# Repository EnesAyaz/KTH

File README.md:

# KTH
This repository is opened to be archival information for my coming Ph.D studies at KTH.

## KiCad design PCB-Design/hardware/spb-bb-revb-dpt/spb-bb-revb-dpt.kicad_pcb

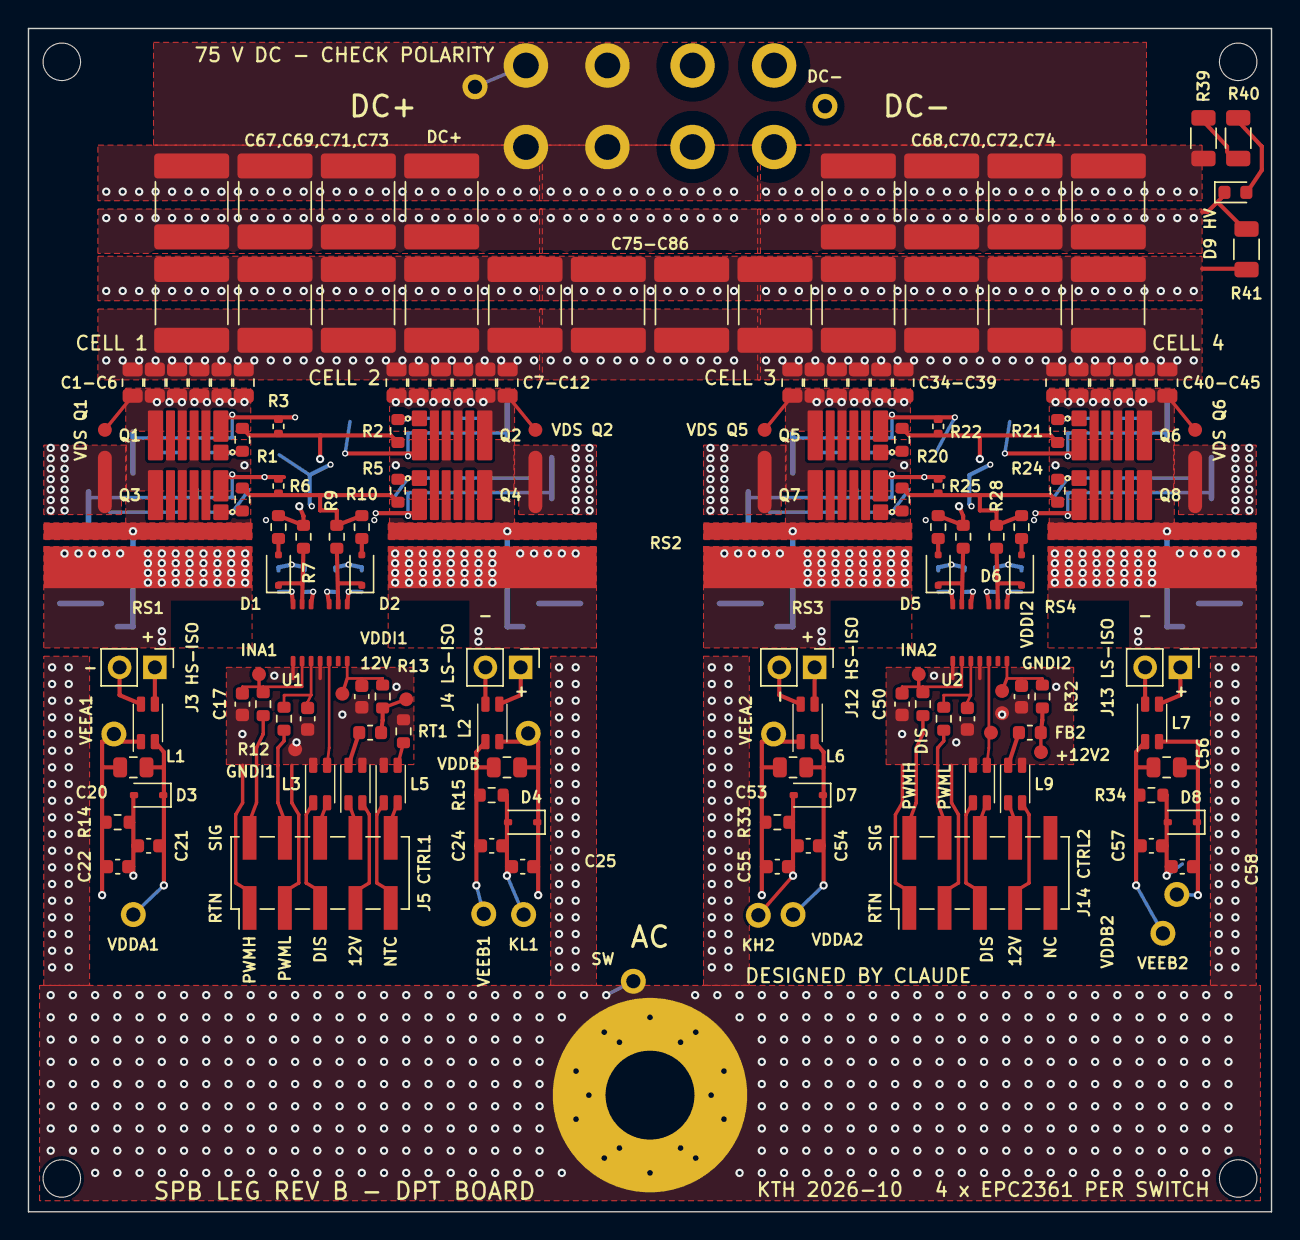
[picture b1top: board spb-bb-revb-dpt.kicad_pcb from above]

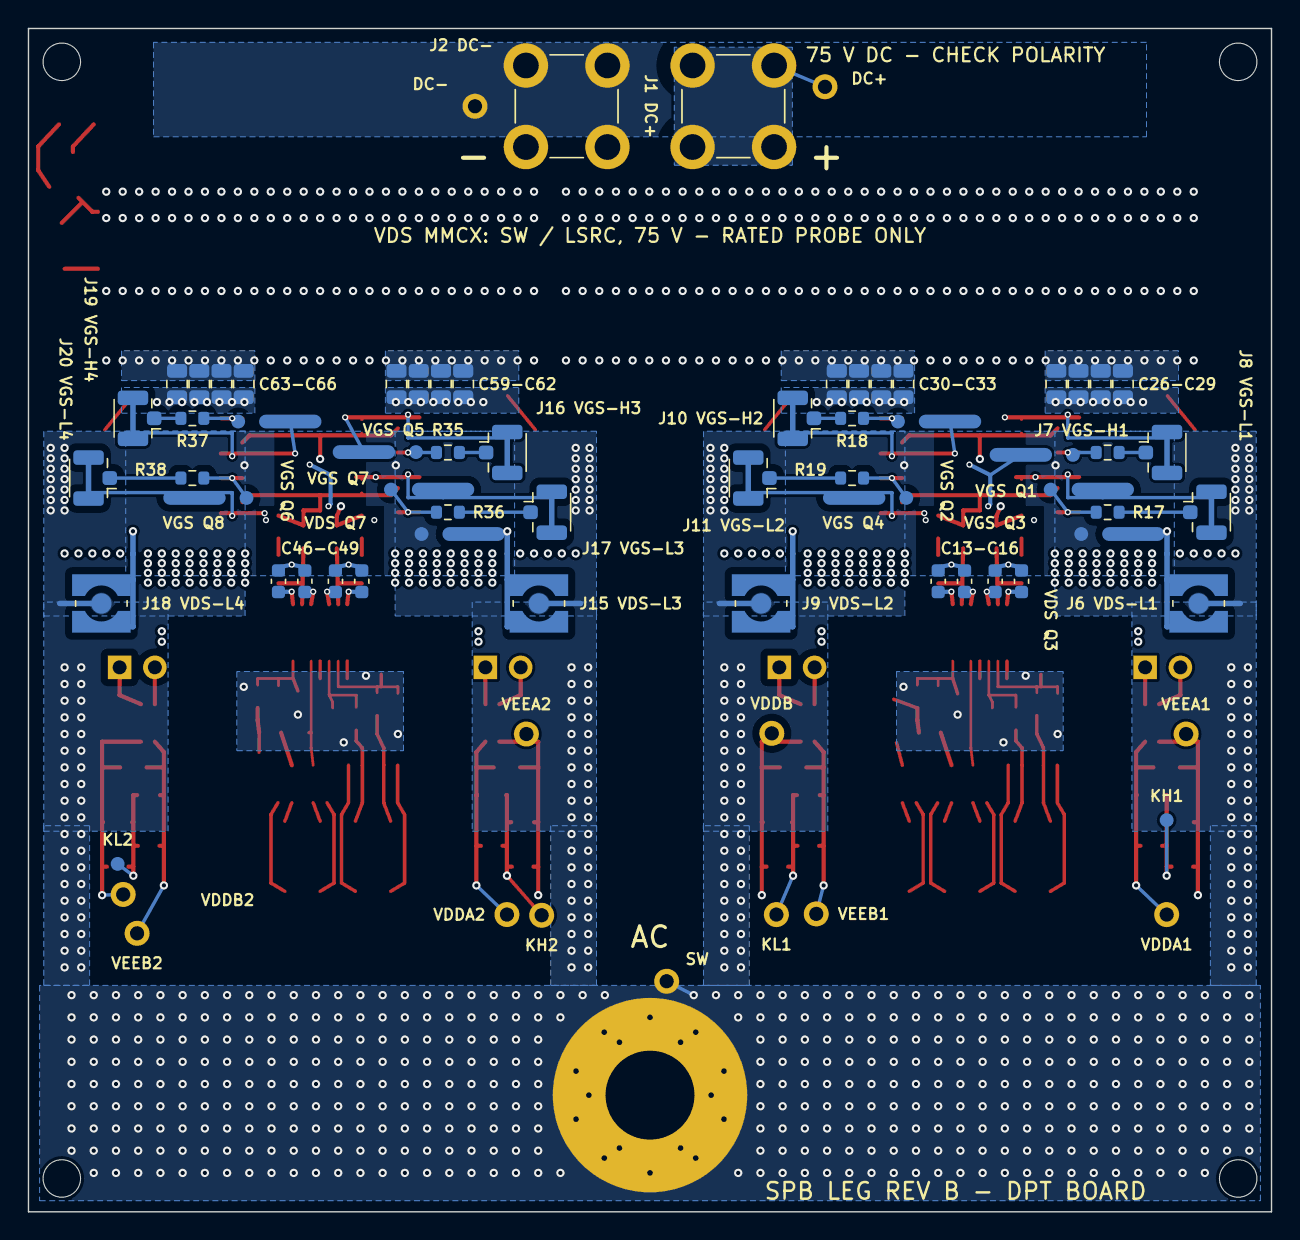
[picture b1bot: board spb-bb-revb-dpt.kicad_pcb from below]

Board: 4 copper layers, 89.5 x 85.2 mm, 225 parts (67 on the bottom side), 86 nets.

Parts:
C1, C2, C3, C4, C5, C6, C7, C8, C9, C10, C11, C12, C26, C27, C28, C29, C30, C31, C32, C33, C34, C35, C36, C37, C38, C39, C40, C41, C42, C43, C44, C45, C59, C60, C61, C62, C63, C64, C65, C66: 1uF 100V X7S; C_0805_2012Metric_TightCrtYd
C13, C14, C15, C16, C46, C47, C48, C49: 1uF 25V X7R 0603; C_0603_1608Metric
C17, C18, C50, C51: 100pF C0G 0603; C_0603_1608Metric
C19, C52: 22nF 25V X7R 0603; C_0603_1608Metric
C20, C23, C53, C56: 4.7uF 25V X7R 0805; C_0805_2012Metric
C21, C22, C24, C25, C54, C55, C57, C58: 4.7uF 16V X5R 0603; C_0603_1608Metric
C67, C68, C69, C70, C71, C72, C73, C74, C75, C76, C77, C78, C79, C80, C81, C82, C83, C84, C85, C86: 22uF 100V X7S 2220; C_2220_5750Metric_TightCrtYd
D1, D2, D5, D6: PMEG3020EJ; D_SOD-323F
D3, D4, D7, D8: BZX384-C5V1; D_SOD-323
D9: red 0603 (DC link present); LED_0603_1608Metric
FB1, FB2: BLM18PG221SN1 (220 R @ 100 MHz); L_0603_1608Metric
H1, H2, H3, H4: M2.5 insulated; MountingHole_2.7mm_M2.5
J1: DC+; Wuerth_REDCUBE-THR_WP-THRBU_74650174_THR
J2: DC-; Wuerth_REDCUBE-THR_WP-THRBU_74650174_THR
J3, J12: V_ISO,HS in: 1 +, 2 -; PinHeader_1x02_P2.54mm_Vertical
J4, J13: V_ISO,LS in: 1 +, 2 -; PinHeader_1x02_P2.54mm_Vertical
J5: CTRL1: 1 RTN 2 PWMH 3 RTN 4 PWML 5 RTN 6 DIS 7 RT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; PinHeader_2x05_P2.54mm_Vertical_SMD
J6: MMCX VDS L1; WR-MMCX_Wuerth_66012102111404_Vertical
J7: U.FL H1; U.FL_Hirose_U.FL-R-SMT-1_Vertical
J8: U.FL L1; U.FL_Hirose_U.FL-R-SMT-1_Vertical
J9: MMCX VDS L2; WR-MMCX_Wuerth_66012102111404_Vertical
J10: U.FL H2; U.FL_Hirose_U.FL-R-SMT-1_Vertical
J11: U.FL L2; U.FL_Hirose_U.FL-R-SMT-1_Vertical
J14: CTRL2: 1 RTN 2 PWMH 3 RTN 4 PWML 5 RTN 6 DIS 7 RT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; PinHeader_2x05_P2.54mm_Vertical_SMD
J15: MMCX VDS L3; WR-MMCX_Wuerth_66012102111404_Vertical
J16: U.FL H3; U.FL_Hirose_U.FL-R-SMT-1_Vertical
J17: U.FL L3; U.FL_Hirose_U.FL-R-SMT-1_Vertical
J18: MMCX VDS L4; WR-MMCX_Wuerth_66012102111404_Vertical
J19: U.FL H4; U.FL_Hirose_U.FL-R-SMT-1_Vertical
J20: U.FL L4; U.FL_Hirose_U.FL-R-SMT-1_Vertical
J21: AC; AC_BOLT_M6
L1, L2, L3, L4, L5, L6, L7, L8, L9: WE-CNSW 744232601; L_CommonMode_Wurth_WE-CNSW-1206
Q1, Q2, Q3, Q4, Q5, Q6, Q7, Q8: EPC2361
R1, R20: 0R5 1% (R_G HL); R_0603_1608Metric
R2, R21: 0R5 1% (R_G HR); R_0603_1608Metric
R3, R22: 10k 1% (HS gate pull-down); R_0402_1005Metric
R4, R23: 0R5 1% (R_G LL); R_0603_1608Metric
R5, R24: 0R5 1% (R_G LR); R_0603_1608Metric
R6, R25: 10k 1% (LS gate pull-down); R_0402_1005Metric
R7, R26: 1R5 1% (R_ON,A); R_0603_1608Metric
R8, R27: 0R (R_OFF,A); R_0603_1608Metric
R9, R28: 1R5 1% (R_ON,B); R_0603_1608Metric
R10, R29: 0R (R_OFF,B); R_0603_1608Metric
R11, R30: 47R 1% (INA); R_0603_1608Metric
R12, R31: 47R 1% (INB); R_0603_1608Metric
R13, R32: 3k 1% (RVDDI); R_0603_1608Metric
R14, R15, R33, R34: 150R 1% 0603 (bias, <= 82 mW); R_0603_1608Metric
R16, R18, R35, R37: DNP 0R (V_GS HS, fit to use the U.FL); R_0603_1608Metric
R17, R19, R36, R38: DNP 0R (V_GS LS, fit to use the U.FL); R_0603_1608Metric
R39, R40: 68k 1206 (HV LED); R_1206_3216Metric
R41: 100k 1206 (bleeder); R_1206_3216Metric
RS1, RS2, RS3, RS4: UFCS-R001; PMK_UFCS_R001_short_IN
RT1: NTC 10k B3380 0603; R_0603_1608Metric
TP1: GNDI1; TestPoint_Pad_D1.0mm
TP2: +12V1; TestPoint_Pad_D1.0mm
TP3: VDDI1; TestPoint_Pad_D1.0mm
TP4: INA1; TestPoint_Pad_D1.0mm
TP7: VDDA1; TestPoint_Keystone5000_Adafruit3825
TP8: VEEA1; TestPoint_Keystone5000_Adafruit3825
TP9: KH1; TestPoint_Pad_D1.0mm
TP11: VDDB1; TestPoint_Keystone5000_Adafruit3825
TP12: VEEB1; TestPoint_Keystone5000_Adafruit3825
TP13: KL1; TestPoint_Keystone5000_Adafruit3825
TP15: VGS Q1; TestPoint_Spring_1.0_GND1.5-6.0
TP16: VGS Q2; TestPoint_Spring_1.0_GND1.5-6.0
TP17: VGS Q3; TestPoint_Spring_1.0_GND1.5-6.0
TP18: VGS Q4; TestPoint_Spring_1.0_GND1.5-6.0
TP19: GNDI2; TestPoint_Pad_D1.0mm
TP20: +12V2; TestPoint_Pad_D1.0mm
TP21: VDDI2; TestPoint_Pad_D1.0mm
TP22: INA2; TestPoint_Pad_D1.0mm
TP24: DIS2; TestPoint_Pad_D1.0mm
TP25: VDDA2; TestPoint_Keystone5000_Adafruit3825
TP26: VEEA2; TestPoint_Keystone5000_Adafruit3825
TP27: KH2; TestPoint_Keystone5000_Adafruit3825
TP29: VDDB2; TestPoint_Keystone5000_Adafruit3825
TP30: VEEB2; TestPoint_Keystone5000_Adafruit3825
TP31: KL2; TestPoint_Pad_D1.0mm
TP33: VGS Q5; TestPoint_Spring_1.0_GND1.5-6.0
TP34: VGS Q6; TestPoint_Spring_1.0_GND1.5-6.0
TP35: VGS Q7; TestPoint_Spring_1.0_GND1.5-6.0
TP36: VGS Q8; TestPoint_Spring_1.0_GND1.5-6.0
TP37: VDS Q3; TestPoint_Spring_1.0_GND1.5-6.0
TP38: VDS Q1; TestPoint_Spring_1.0_GND1.5-6.0
TP40: VDS Q2; TestPoint_Spring_1.0_GND1.5-6.0
TP41: VDS Q7; TestPoint_Spring_1.0_GND1.5-6.0
TP42: VDS Q5; TestPoint_Spring_1.0_GND1.5-6.0
TP44: VDS Q6; TestPoint_Spring_1.0_GND1.5-6.0
TP45: DC+; TestPoint_Keystone5000_Adafruit3825
TP46: DC-; TestPoint_Keystone5000_Adafruit3825
TP47: SW; TestPoint_Keystone5000_Adafruit3825
U1, U2: 2EDF7275K; 2EDF7275K_PG-TFLGA-13-4

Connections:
12V_CM1: FB1.1, L4.2
12V_CM2: FB2.1, L9.2
+12V1: FB1.2, R13.1, TP2.1
+12V2: FB2.2, R32.1, TP20.1
C_12V1: J5.8, L4.1
C_12V2: J14.8, L9.1
C_DIS1: J5.6, L3.4
C_DIS2: J14.6, L8.4
C_NTC1: J5.10, L5.4
C_RTN_12V1: J5.7, L4.4
C_RTN_12V2: J14.7, L9.4
C_RTN_DIS1: J5.5, L3.1
C_RTN_DIS2: J14.5, L8.1
C_RTN_NTC1: J5.9, L5.1
DCN: C1.2, C2.2, C3.2, C4.2, C5.2, C6.2, C7.2, C8.2, C9.2, C10.2, C11.2, C12.2, C26.1, C27.1, C28.1, C29.1, C30.1, C31.1, C32.1, C33.1, C34.2, C35.2, C36.2, C37.2, C38.2, C39.2, C40.2, C41.2, C42.2, C43.2, C44.2, C45.2, C59.1, C60.1, C61.1, C62.1, C63.1, C64.1, C65.1, C66.1, C67.1, C68.1, C69.1, C70.1, C71.1, C72.1, C73.1, C74.1, C75.1, C76.1, C77.1, C78.1, C79.1, C80.1, C81.1, C82.1, C83.1, C84.1, C85.1, C86.1, D9.1, J2.1, R41.2, RS1.2, RS2.2, RS3.2, RS4.2, TP46.1
DCP: C1.1, C2.1, C3.1, C4.1, C5.1, C6.1, C7.1, C8.1, C9.1, C10.1, C11.1, C12.1, C26.2, C27.2, C28.2, C29.2, C30.2, C31.2, C32.2, C33.2, C34.1, C35.1, C36.1, C37.1, C38.1, C39.1, C40.1, C41.1, C42.1, C43.1, C44.1, C45.1, C59.2, C60.2, C61.2, C62.2, C63.2, C64.2, C65.2, C66.2, C67.2, C68.2, C69.2, C70.2, C71.2, C72.2, C73.2, C74.2, C75.2, C76.2, C77.2, C78.2, C79.2, C80.2, C81.2, C82.2, C83.2, C84.2, C85.2, C86.2, J1.1, Q1.3, Q1.5, Q1.7, Q2.3, Q2.5, Q2.7, Q5.3, Q5.5, Q5.7, Q6.3, Q6.5, Q6.7, R39.1, R41.1, TP38.1, TP40.1, TP42.1, TP44.1, TP45.1
DIS1: L3.3, U1.5
DIS2: L8.3, TP24.1, U2.5
GH_L1: Q1.1, R1.1, R16.2, TP15.1
GH_L2: Q5.1, R20.1, R35.2, TP33.1
GH_R1: Q2.1, R2.2, R18.1, TP16.1
GH_R2: Q6.1, R21.2, R37.1, TP34.1
GH_STAR1: R1.2, R2.1, R3.1, R7.2, R8.2
GH_STAR2: R20.2, R21.1, R22.1, R26.2, R27.2
GL_L1: Q3.1, R4.1, R17.2, TP17.1
GL_L2: Q7.1, R23.1, R36.2, TP35.1
GL_R1: Q4.1, R5.2, R19.1, TP18.1
GL_R2: Q8.1, R24.2, R38.1, TP36.1
GL_STAR1: R4.2, R5.1, R6.1, R9.2, R10.2
GL_STAR2: R23.2, R24.1, R25.1, R28.2, R29.2
GNDI1: C17.1, C18.1, C19.1, J5.1, J5.3, L3.2, L4.3, L5.2, RT1.2, TP1.1, U1.1, U1.4
GNDI2: C50.1, C51.1, C52.1, J14.1, J14.3, L8.2, L9.3, TP19.1, U2.1, U2.4
HVA: R39.2, R40.1
HVB: D9.2, R40.2
INA1: C17.2, R11.2, TP4.1, U1.2
INA2: C50.2, R30.2, TP22.1, U2.2
INB1: C18.2, R12.2, U1.3
INB2: C51.2, R31.2, U2.3
KH1: C13.1, C14.1, C21.1, C22.2, D3.2, J7.2, J10.2, Q1.2, Q2.2, R3.2, R14.2, TP9.1, TP15.2, TP16.2
KH2: C46.1, C47.1, C54.1, C55.2, D7.2, J16.2, J19.2, Q5.2, Q6.2, R22.2, R33.2, TP27.1, TP33.2, TP34.2
KL1: C15.1, C16.1, C24.2, C25.1, D4.2, J8.2, J11.2, Q3.2, Q4.2, R6.2, R15.2, TP13.1, TP17.2, TP18.2
KL2: C48.1, C49.1, C57.2, C58.1, D8.2, J17.2, J20.2, Q7.2, Q8.2, R25.2, R34.2, TP31.1, TP35.2, TP36.2
LSRC1: J6.2, Q3.4, Q3.6, RS1.1, TP37.2
LSRC2: J9.2, Q4.4, Q4.6, RS2.1
LSRC3: J15.2, Q7.4, Q7.6, RS3.1, TP41.2
LSRC4: J18.2, Q8.4, Q8.6, RS4.1
NTC: L5.3, RT1.1
OFFA1: D1.2, R8.1
OFFA2: D5.2, R27.1
OFFB1: D2.2, R10.1
OFFB2: D6.2, R29.1
OUTA1: D1.1, R7.1, U1.12
OUTA2: D5.1, R26.1, U2.12
OUTB1: D2.1, R9.1, U1.9
OUTB2: D6.1, R28.1, U2.9
PWM_H1: J5.2, R11.1
PWM_H2: J14.2, R30.1
PWM_L1: J5.4, R12.1
PWM_L2: J14.4, R31.1
SW: J6.1, J9.1, J15.1, J18.1, J21.1, Q1.4, Q1.6, Q2.4, Q2.6, Q3.3, Q3.5, Q3.7, Q4.3, Q4.5, Q4.7, Q5.4, Q5.6, Q6.4, Q6.6, Q7.3, Q7.5, Q7.7, Q8.3, Q8.5, Q8.7, TP37.1, TP38.2, TP40.2, TP41.1, TP42.2, TP44.2, TP47.1
UFL_H1: J7.1, R16.1
UFL_H2: J10.1, R18.2
UFL_H3: J16.1, R35.1
UFL_H4: J19.1, R37.2
UFL_L1: J8.1, R17.1
UFL_L2: J11.1, R19.2
UFL_L3: J17.1, R36.1
UFL_L4: J20.1, R38.2
VDDA1: C13.2, C20.2, C21.2, D3.1, L1.4, TP7.1, U1.13
VDDA2: C46.2, C53.2, C54.2, D7.1, L6.4, TP25.1, U2.13
VDDB1: C16.2, C23.2, C25.2, D4.1, L2.4, TP11.1, U1.10
VDDB2: C49.2, C56.2, C58.2, D8.1, L7.4, TP29.1, U2.10
VDDI1: C19.2, R13.2, TP3.1, U1.7
VDDI2: C52.2, R32.2, TP21.1, U2.7
VEEA1: C14.2, C20.1, C22.1, L1.1, R14.1, TP8.1, U1.11
VEEA2: C47.2, C53.1, C55.1, L6.1, R33.1, TP26.1, U2.11
VEEB1: C15.2, C23.1, C24.1, L2.1, R15.1, TP12.1, U1.8
VEEB2: C48.2, C56.1, C57.1, L7.1, R34.1, TP30.1, U2.8
VINA_N1: J3.2, L1.2
VINA_N2: J12.2, L6.2
VINA_P1: J3.1, L1.3
VINA_P2: J12.1, L6.3
VINB_N1: J4.2, L2.2
VINB_N2: J13.2, L7.2
VINB_P1: J4.1, L2.3
VINB_P2: J13.1, L7.3

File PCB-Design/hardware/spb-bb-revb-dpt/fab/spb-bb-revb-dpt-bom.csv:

"# 4 layers, 1.6 mm FR4, 2 oz (70 um) on all layers, L1-L2 and L3-L4 prepreg 0.1 mm, ENIG; filled + capped via-in-pad (list in gerber/*-fab-notes.txt: shunt SHLD, bypass-capacitor and test pads); double-pulse board (UFCS shunts, no heatsink); IPC class 2; solder mask over all copper and ALL vias tented (the 1200 V control/power barrier relies on it)"
Qty,References,Value,Footprint,Manufacturer part / note,Fit
1,J1,DC+,Wuerth_REDCUBE-THR_WP-THRBU_74650174_THR,"Wuerth 74650174 (REDCUBE THR, M4)",fit
1,J2,DC-,Wuerth_REDCUBE-THR_WP-THRBU_74650174_THR,"Wuerth 74650174 (REDCUBE THR, M4)",fit
8,Q1 Q2 Q3 Q4 Q5 Q6 Q7 Q8,EPC2361,EPC2361,EPC2361,fit
40,C1 C2 C3 C4 C5 C6 C7 C8 C9 C10 C11 C12 C26 C27 C28 C29 C30 C31 C32 C33 C34 C35 C36 C37 C38 C39 C40 C41 C42 C43 C44 C45 C59 C60 C61 C62 C63 C64 C65 C66,1uF 100V X7S,C_0805_2012Metric_TightCrtYd,TDK C2012X7S2A105K125AB,fit
2,R1 R20,0R5 1% (R_G HL),R_0603_1608Metric,0.5R 0603 1% (Panasonic ERJ-3BQFR50V),fit
2,R2 R21,0R5 1% (R_G HR),R_0603_1608Metric,0.5R 0603 1% (Panasonic ERJ-3BQFR50V),fit
2,R3 R22,10k 1% (HS gate pull-down),R_0402_1005Metric,10k 0402 1%,fit
2,R4 R23,0R5 1% (R_G LL),R_0603_1608Metric,0.5R 0603 1% (Panasonic ERJ-3BQFR50V),fit
2,R5 R24,0R5 1% (R_G LR),R_0603_1608Metric,0.5R 0603 1% (Panasonic ERJ-3BQFR50V),fit
2,R6 R25,10k 1% (LS gate pull-down),R_0402_1005Metric,10k 0402 1%,fit
2,U1 U2,2EDF7275K,2EDF7275K_PG-TFLGA-13-4,Infineon 2EDF7275KXUMA1,fit
2,R7 R26,"1R5 1% (R_ON,A)",R_0603_1608Metric,1.5R 0603 1% (Yageo RC0603FR-071R5L),fit
2,R8 R27,"0R (R_OFF,A)",R_0603_1608Metric,0R 0603 jumper (set R_OFF here),fit
4,D1 D2 D5 D6,PMEG3020EJ,D_SOD-323F,"Nexperia PMEG3020EJ (30 V, 2 A, SOD323F)",fit
2,R9 R28,"1R5 1% (R_ON,B)",R_0603_1608Metric,1.5R 0603 1% (Yageo RC0603FR-071R5L),fit
2,R10 R29,"0R (R_OFF,B)",R_0603_1608Metric,0R 0603 jumper (set R_OFF here),fit
8,C13 C14 C15 C16 C46 C47 C48 C49,1uF 25V X7R 0603,C_0603_1608Metric,TDK C1608X7R1E105K080AB,fit
4,C17 C18 C50 C51,100pF C0G 0603,C_0603_1608Metric,Murata GRM1885C1H101JA01,fit
2,R11 R30,47R 1% (INA),R_0603_1608Metric,47R 0603 1%,fit
2,R12 R31,47R 1% (INB),R_0603_1608Metric,47R 0603 1%,fit
2,C19 C52,22nF 25V X7R 0603,C_0603_1608Metric,Murata GRM188R71E223KA01,fit
2,R13 R32,3k 1% (RVDDI),R_0603_1608Metric,3.0k 0603 1%,fit
4,RS1 RS2 RS3 RS4,UFCS-R001,PMK_UFCS_R001_short_IN,"PMK UFCS-R001 (1 mOhm, 50 A cont.)","NOT by the assembler: hand-soldered in the lab at the blade (short IN land), SMA cable to the scope"
2,J3 J12,"V_ISO,HS in: 1 +, 2 -",PinHeader_1x02_P2.54mm_Vertical,2.54 mm header 1x2,fit
9,L1 L2 L3 L4 L5 L6 L7 L8 L9,WE-CNSW 744232601,L_CommonMode_Wurth_WE-CNSW-1206,"Wurth 744232601 (600 Ohm @ 100 MHz, 260 mA)",fit
4,C20 C23 C53 C56,4.7uF 25V X7R 0805,C_0805_2012Metric,Murata GRM21BR71E475KA73,fit
4,D3 D4 D7 D8,BZX384-C5V1,D_SOD-323,"Nexperia BZX384-C5V1 (5.1 V, 300 mW)",fit
4,R14 R15 R33 R34,"150R 1% 0603 (bias, <= 82 mW)",R_0603_1608Metric,150R 0603 1% 0.1 W,fit
8,C21 C22 C24 C25 C54 C55 C57 C58,4.7uF 16V X5R 0603,C_0603_1608Metric,Murata GRM188R61C475KAAJ,fit
2,J4 J13,"V_ISO,LS in: 1 +, 2 -",PinHeader_1x02_P2.54mm_Vertical,2.54 mm header 1x2,fit
1,J5,CTRL1: 1 RTN 2 PWMH 3 RTN 4 PWML 5 RTN 6 DIS 7 RTN 8 12V 9 RTN 10 NTC,PinHeader_2x05_P2.54mm_Vertical_SMD,"Samtec TSM-105-01-T-DV (2 x 5, 2.54 mm, SMT)",fit
2,FB1 FB2,BLM18PG221SN1 (220 R @ 100 MHz),L_0603_1608Metric,"Murata BLM18PG221SN1D (ferrite bead, 1.4 A)",fit
1,RT1,NTC 10k B3380 0603,R_0603_1608Metric,Murata NCP18XH103F03RB,fit
1,J6,MMCX VDS L1,WR-MMCX_Wuerth_66012102111404_Vertical,"Wurth 66012102111404 (WR-MMCX PCB SMT jack, vertical, 170 V rms)",fit
1,J7,U.FL H1,U.FL_Hirose_U.FL-R-SMT-1_Vertical,Hirose U.FL-R-SMT-1(10),fit
4,R16 R18 R35 R37,"DNP 0R (V_GS HS, fit to use the U.FL)",R_0603_1608Metric,0R 0603 - not fitted by default,DNP
1,J8,U.FL L1,U.FL_Hirose_U.FL-R-SMT-1_Vertical,Hirose U.FL-R-SMT-1(10),fit
4,R17 R19 R36 R38,"DNP 0R (V_GS LS, fit to use the U.FL)",R_0603_1608Metric,0R 0603 - not fitted by default,DNP
1,J9,MMCX VDS L2,WR-MMCX_Wuerth_66012102111404_Vertical,"Wurth 66012102111404 (WR-MMCX PCB SMT jack, vertical, 170 V rms)",fit
1,J10,U.FL H2,U.FL_Hirose_U.FL-R-SMT-1_Vertical,Hirose U.FL-R-SMT-1(10),fit
1,J11,U.FL L2,U.FL_Hirose_U.FL-R-SMT-1_Vertical,Hirose U.FL-R-SMT-1(10),fit
1,J14,CTRL2: 1 RTN 2 PWMH 3 RTN 4 PWML 5 RTN 6 DIS 7 RTN 8 12V 9 NC 10 NC,PinHeader_2x05_P2.54mm_Vertical_SMD,"Samtec TSM-105-01-T-DV (2 x 5, 2.54 mm, SMT)",fit
1,J15,MMCX VDS L3,WR-MMCX_Wuerth_66012102111404_Vertical,"Wurth 66012102111404 (WR-MMCX PCB SMT jack, vertical, 170 V rms)",fit
1,J16,U.FL H3,U.FL_Hirose_U.FL-R-SMT-1_Vertical,Hirose U.FL-R-SMT-1(10),fit
1,J17,U.FL L3,U.FL_Hirose_U.FL-R-SMT-1_Vertical,Hirose U.FL-R-SMT-1(10),fit
1,J18,MMCX VDS L4,WR-MMCX_Wuerth_66012102111404_Vertical,"Wurth 66012102111404 (WR-MMCX PCB SMT jack, vertical, 170 V rms)",fit
1,J19,U.FL H4,U.FL_Hirose_U.FL-R-SMT-1_Vertical,Hirose U.FL-R-SMT-1(10),fit
1,J20,U.FL L4,U.FL_Hirose_U.FL-R-SMT-1_Vertical,Hirose U.FL-R-SMT-1(10),fit
20,C67 C68 C69 C70 C71 C72 C73 C74 C75 C76 C77 C78 C79 C80 C81 C82 C83 C84 C85 C86,22uF 100V X7S 2220,C_2220_5750Metric_TightCrtYd,TDK C5750X7S2A226M280KB,fit
2,R39 R40,68k 1206 (HV LED),R_1206_3216Metric,68k 1206 1% 200 V,fit
1,D9,red 0603 (DC link present),LED_0603_1608Metric,Wurth 150060RS75000,fit
1,R41,100k 1206 (bleeder),R_1206_3216Metric,100k 1206 1% 200 V,fit

Mechanical (not placed by the assembler)
2,J1-J2,M4 x 8 screw + washer into REDCUBE (to the DC source / busbar),-,"steel, A2"
1,J21,"M6 x 16 bolt + nut + 2 washers, AC bolt pad",-,"steel, A2"
1,J21,"AC bar 12 x 5 mm Cu, M6 hole, length to the load inductor",-,"Cu-ETP, tin plated"
4,H1-H4,M2.5 standoff + screw (board mounting),-,nylon / insulated
2,"J5, J14",Control cable: 2 x 5 IDC socket + ribbon (each signal next to its own return),-,"2.54 mm IDC, e.g. Wurth 61201021621"
13,TP7 TP8 TP11 TP12 TP13 TP25 TP26 TP27 TP29 TP30 TP45 TP46 TP47,"Loop test point, red, 0.1 in bushing, 1.02 mm (0.040 in) hole (inserted in the lab, not by the assembler; see fab/testpoints.csv)",TestPoint_Keystone5000_Adafruit3825,"Adafruit 3825 (PiShop 1752), equivalent Keystone 5000 (red) / 5001 (black)"

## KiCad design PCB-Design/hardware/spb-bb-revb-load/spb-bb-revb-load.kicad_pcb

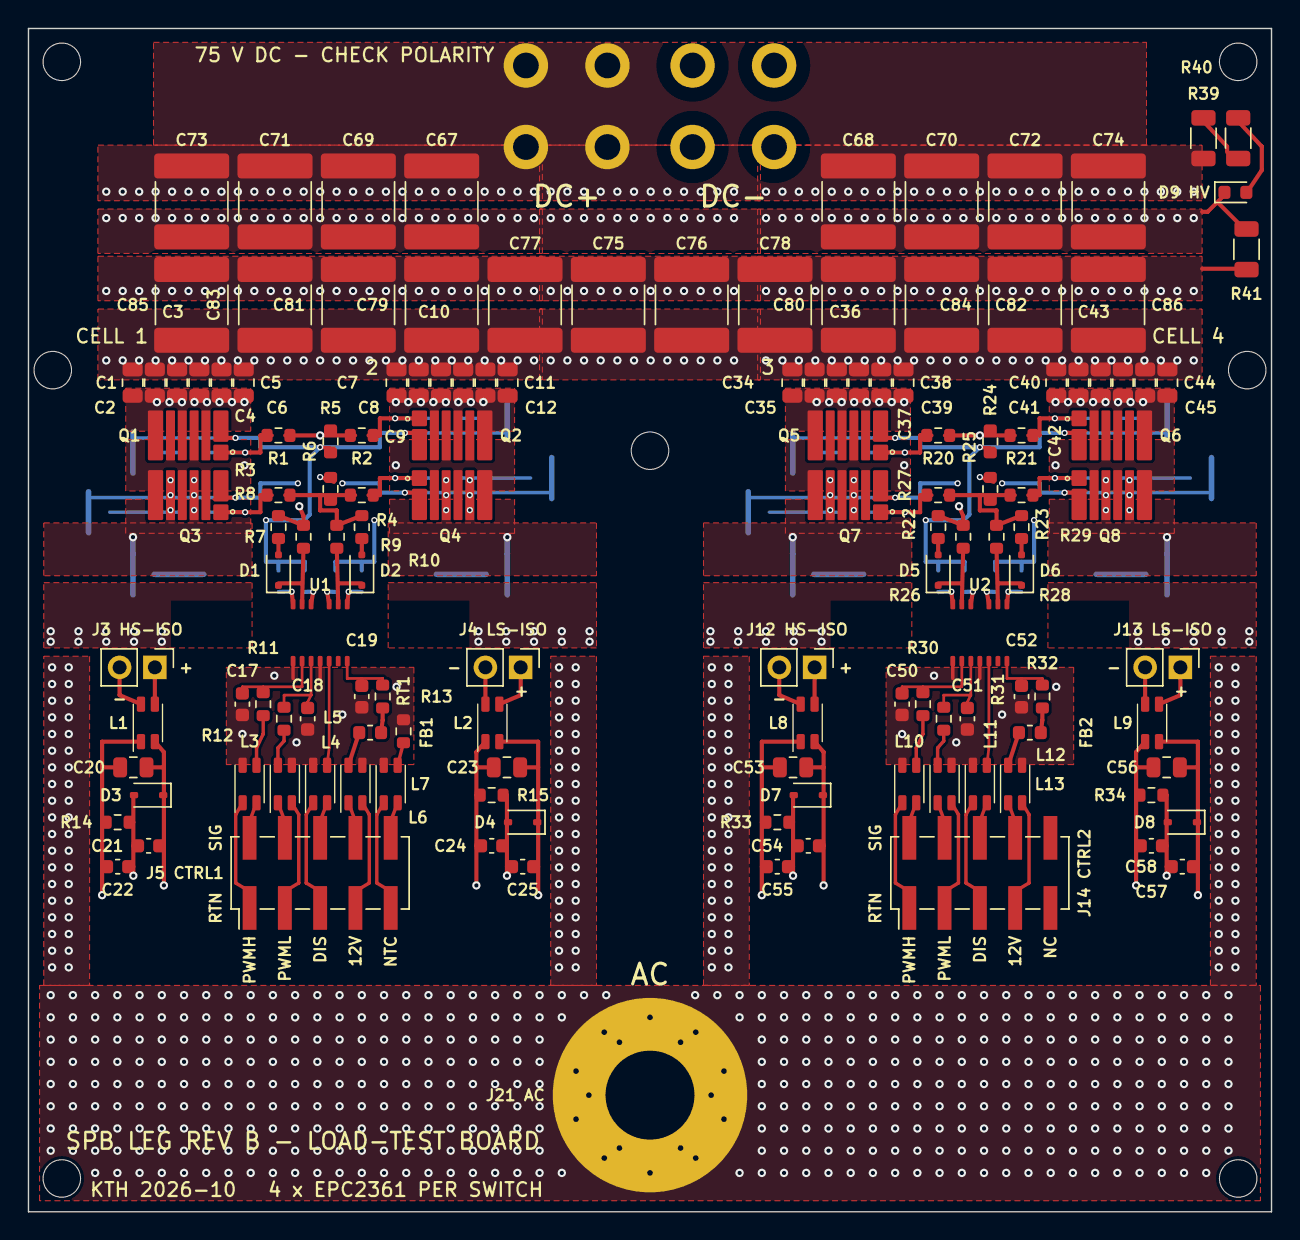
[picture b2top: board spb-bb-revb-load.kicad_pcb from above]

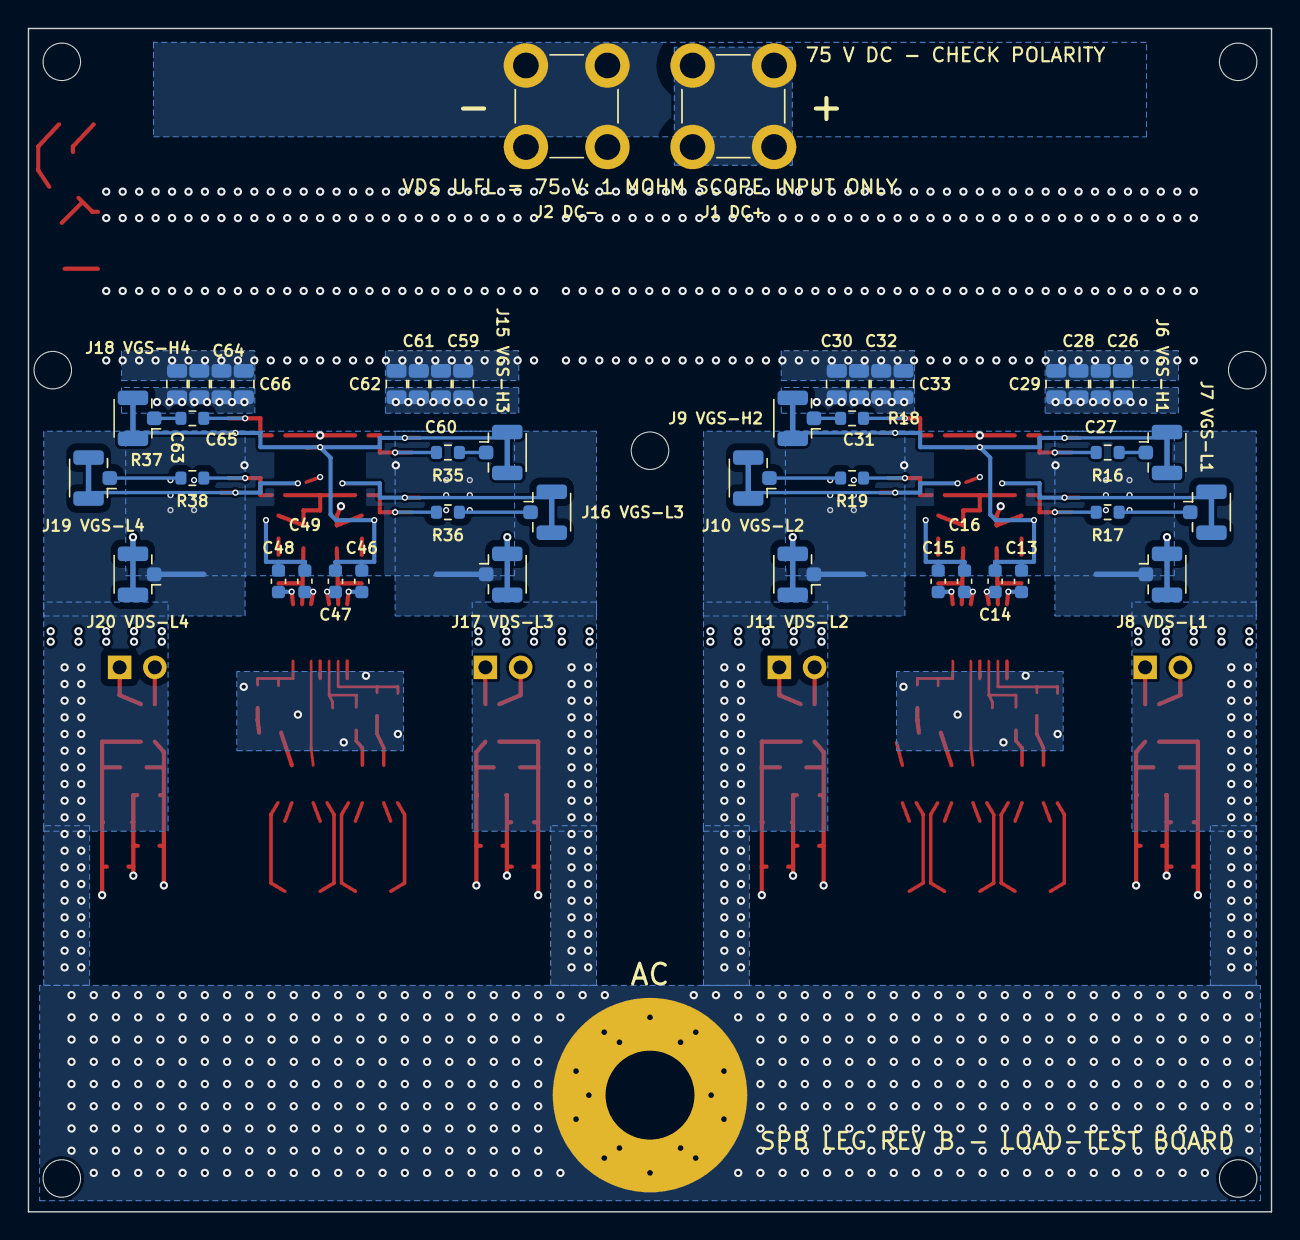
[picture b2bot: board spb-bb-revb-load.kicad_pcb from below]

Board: 4 copper layers, 89.5 x 85.2 mm, 191 parts (46 on the bottom side), 90 nets.

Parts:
C1, C2, C3, C4, C5, C6, C7, C8, C9, C10, C11, C12, C26, C27, C28, C29, C30, C31, C32, C33, C34, C35, C36, C37, C38, C39, C40, C41, C42, C43, C44, C45, C59, C60, C61, C62, C63, C64, C65, C66: 1uF 100V X7S; C_0805_2012Metric_TightCrtYd
C13, C14, C15, C16, C46, C47, C48, C49: 1uF 25V X7R 0603; C_0603_1608Metric
C17, C18, C50, C51: 100pF C0G 0603; C_0603_1608Metric
C19, C52: 22nF 25V X7R 0603; C_0603_1608Metric
C20, C23, C53, C56: 4.7uF 25V X7R 0805; C_0805_2012Metric
C21, C22, C24, C25, C54, C55, C57, C58: 4.7uF 16V X5R 0603; C_0603_1608Metric
C67, C68, C69, C70, C71, C72, C73, C74, C75, C76, C77, C78, C79, C80, C81, C82, C83, C84, C85, C86: 22uF 100V X7S 2220; C_2220_5750Metric_TightCrtYd
D1, D2, D5, D6: PMEG3020EJ; D_SOD-323F
D3, D4, D7, D8: BZX384-C5V1; D_SOD-323
D9: red 0603 (DC link present); LED_0603_1608Metric
FB1, FB2: BLM18PG221SN1 (220 R @ 100 MHz); L_0603_1608Metric
H1, H2, H3, H4: M2.5 insulated; MountingHole_2.7mm_M2.5
H5, H6, H7: M2.5 heatsink spreader; MountingHole_2.7mm_M2.5
HS1: Fischer LAM 4 K 50 12 + spreader; HS_LAM4K5012_revb
J1: DC+; Wuerth_REDCUBE-THR_WP-THRBU_74650174_THR
J2: DC-; Wuerth_REDCUBE-THR_WP-THRBU_74650174_THR
J3, J12: V_ISO,HS in: 1 +, 2 -; PinHeader_1x02_P2.54mm_Vertical
J4, J13: V_ISO,LS in: 1 +, 2 -; PinHeader_1x02_P2.54mm_Vertical
J5: CTRL1: 1 RTN 2 PWMH 3 RTN 4 PWML 5 RTN 6 DIS 7 RT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; PinHeader_2x05_P2.54mm_Vertical_SMD
J6: U.FL H1; U.FL_Hirose_U.FL-R-SMT-1_Vertical
J7: U.FL L1; U.FL_Hirose_U.FL-R-SMT-1_Vertical
J8: U.FL D1; U.FL_Hirose_U.FL-R-SMT-1_Vertical
J9: U.FL H2; U.FL_Hirose_U.FL-R-SMT-1_Vertical
J10: U.FL L2; U.FL_Hirose_U.FL-R-SMT-1_Vertical
J11: U.FL D2; U.FL_Hirose_U.FL-R-SMT-1_Vertical
J14: CTRL2: 1 RTN 2 PWMH 3 RTN 4 PWML 5 RTN 6 DIS 7 RT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; PinHeader_2x05_P2.54mm_Vertical_SMD
J15: U.FL H3; U.FL_Hirose_U.FL-R-SMT-1_Vertical
J16: U.FL L3; U.FL_Hirose_U.FL-R-SMT-1_Vertical
J17: U.FL D3; U.FL_Hirose_U.FL-R-SMT-1_Vertical
J18: U.FL H4; U.FL_Hirose_U.FL-R-SMT-1_Vertical
J19: U.FL L4; U.FL_Hirose_U.FL-R-SMT-1_Vertical
J20: U.FL D4; U.FL_Hirose_U.FL-R-SMT-1_Vertical
J21: AC; AC_BOLT_M6
L1, L2, L3, L4, L5, L6, L7, L8, L9, L10, L11, L12, L13: WE-CNSW 744232601; L_CommonMode_Wurth_WE-CNSW-1206
Q1, Q2, Q3, Q4, Q5, Q6, Q7, Q8: EPC2361
R1, R20: 0R5 1% (R_G HL); R_0603_1608Metric
R2, R21: 0R5 1% (R_G HR); R_0603_1608Metric
R3, R22: 0R5 1% (R_G LL); R_0603_1608Metric
R4, R23: 0R5 1% (R_G LR); R_0603_1608Metric
R5, R24: 10k 1% (HS gate pull-down); R_0603_1608Metric
R6, R25: 10k 1% (LS gate pull-down); R_0603_1608Metric
R7, R26: 0R75 1% (R_ON,A); R_0603_1608Metric
R8, R27: 0R (R_OFF,A); R_0603_1608Metric
R9, R28: 0R75 1% (R_ON,B); R_0603_1608Metric
R10, R29: 0R (R_OFF,B); R_0603_1608Metric
R11, R30: 47R 1% (INA); R_0603_1608Metric
R12, R31: 47R 1% (INB); R_0603_1608Metric
R13, R32: 3k 1% (RVDDI); R_0603_1608Metric
R14, R15, R33, R34: 150R 1% 0603 (bias, <= 82 mW); R_0603_1608Metric
R16, R18, R35, R37: 0R (V_GS HS); R_0603_1608Metric
R17, R19, R36, R38: 0R (V_GS LS); R_0603_1608Metric
R39, R40: 68k 1206 (HV LED); R_1206_3216Metric
R41: 100k 1206 (bleeder); R_1206_3216Metric
RT1: NTC 10k B3380 0603; R_0603_1608Metric
U1, U2: 2EDF7275K; 2EDF7275K_PG-TFLGA-13-4

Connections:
12V_CM1: FB1.1, L6.2
12V_CM2: FB2.1, L13.2
+12V1: FB1.2, R13.1
+12V2: FB2.2, R32.1
C_12V1: J5.8, L6.1
C_12V2: J14.8, L13.1
C_DIS1: J5.6, L5.4
C_DIS2: J14.6, L12.4
C_NTC1: J5.10, L7.4
C_PWMH1: J5.2, L3.4
C_PWMH2: J14.2, L10.4
C_PWML1: J5.4, L4.1
C_PWML2: J14.4, L11.1
C_RTN_12V1: J5.7, L6.4
C_RTN_12V2: J14.7, L13.4
C_RTN_DIS1: J5.5, L5.1
C_RTN_DIS2: J14.5, L12.1
C_RTN_NTC1: J5.9, L7.1
C_RTN_PWMH1: J5.1, L3.1
C_RTN_PWMH2: J14.1, L10.1
C_RTN_PWML1: J5.3, L4.4
C_RTN_PWML2: J14.3, L11.4
DCN: C1.2, C2.2, C3.2, C4.2, C5.2, C6.2, C7.2, C8.2, C9.2, C10.2, C11.2, C12.2, C26.1, C27.1, C28.1, C29.1, C30.1, C31.1, C32.1, C33.1, C34.2, C35.2, C36.2, C37.2, C38.2, C39.2, C40.2, C41.2, C42.2, C43.2, C44.2, C45.2, C59.1, C60.1, C61.1, C62.1, C63.1, C64.1, C65.1, C66.1, C67.1, C68.1, C69.1, C70.1, C71.1, C72.1, C73.1, C74.1, C75.1, C76.1, C77.1, C78.1, C79.1, C80.1, C81.1, C82.1, C83.1, C84.1, C85.1, C86.1, D9.1, J2.1, J8.2, J11.2, J17.2, J20.2, Q3.4, Q3.6, Q4.4, Q4.6, Q7.4, Q7.6, Q8.4, Q8.6, R41.2
DCP: C1.1, C2.1, C3.1, C4.1, C5.1, C6.1, C7.1, C8.1, C9.1, C10.1, C11.1, C12.1, C26.2, C27.2, C28.2, C29.2, C30.2, C31.2, C32.2, C33.2, C34.1, C35.1, C36.1, C37.1, C38.1, C39.1, C40.1, C41.1, C42.1, C43.1, C44.1, C45.1, C59.2, C60.2, C61.2, C62.2, C63.2, C64.2, C65.2, C66.2, C67.2, C68.2, C69.2, C70.2, C71.2, C72.2, C73.2, C74.2, C75.2, C76.2, C77.2, C78.2, C79.2, C80.2, C81.2, C82.2, C83.2, C84.2, C85.2, C86.2, J1.1, Q1.3, Q1.5, Q1.7, Q2.3, Q2.5, Q2.7, Q5.3, Q5.5, Q5.7, Q6.3, Q6.5, Q6.7, R39.1, R41.1
DIS1: L5.3, U1.5
DIS2: L12.3, U2.5
GH_L1: Q1.1, R1.1, R16.2
GH_L2: Q5.1, R20.1, R35.2
GH_R1: Q2.1, R2.2, R18.1
GH_R2: Q6.1, R21.2, R37.1
GH_STAR1: R1.2, R2.1, R5.2, R7.2, R8.2
GH_STAR2: R20.2, R21.1, R24.2, R26.2, R27.2
GL_L1: Q3.1, R3.1, R17.2
GL_L2: Q7.1, R22.1, R36.2
GL_R1: Q4.1, R4.2, R19.1
GL_R2: Q8.1, R23.2, R38.1
GL_STAR1: R3.2, R4.1, R6.1, R9.2, R10.2
GL_STAR2: R22.2, R23.1, R25.1, R28.2, R29.2
GNDI1: C17.1, C18.1, C19.1, L3.2, L4.3, L5.2, L6.3, L7.2, RT1.2, U1.1, U1.4
GNDI2: C50.1, C51.1, C52.1, L10.2, L11.3, L12.2, L13.3, U2.1, U2.4
HVA: R39.2, R40.1
HVB: D9.2, R40.2
INA1: C17.2, R11.2, U1.2
INA2: C50.2, R30.2, U2.2
INB1: C18.2, R12.2, U1.3
INB2: C51.2, R31.2, U2.3
KH1: C13.1, C14.1, C21.1, C22.2, D3.2, J6.2, J9.2, Q1.2, Q2.2, R5.1, R14.2
KH2: C46.1, C47.1, C54.1, C55.2, D7.2, J15.2, J18.2, Q5.2, Q6.2, R24.1, R33.2
KL1: C15.1, C16.1, C24.2, C25.1, D4.2, J7.2, J10.2, Q3.2, Q4.2, R6.2, R15.2
KL2: C48.1, C49.1, C57.2, C58.1, D8.2, J16.2, J19.2, Q7.2, Q8.2, R25.2, R34.2
NTC: L7.3, RT1.1
OFFA1: D1.2, R8.1
OFFA2: D5.2, R27.1
OFFB1: D2.2, R10.1
OFFB2: D6.2, R29.1
OUTA1: D1.1, R7.1, U1.12
OUTA2: D5.1, R26.1, U2.12
OUTB1: D2.1, R9.1, U1.9
OUTB2: D6.1, R28.1, U2.9
PWM_H1: L3.3, R11.1
PWM_H2: L10.3, R30.1
PWM_L1: L4.2, R12.1
PWM_L2: L11.2, R31.1
SW: J8.1, J11.1, J17.1, J20.1, J21.1, Q1.4, Q1.6, Q2.4, Q2.6, Q3.3, Q3.5, Q3.7, Q4.3, Q4.5, Q4.7, Q5.4, Q5.6, Q6.4, Q6.6, Q7.3, Q7.5, Q7.7, Q8.3, Q8.5, Q8.7
UFL_H1: J6.1, R16.1
UFL_H2: J9.1, R18.2
UFL_H3: J15.1, R35.1
UFL_H4: J18.1, R37.2
UFL_L1: J7.1, R17.1
UFL_L2: J10.1, R19.2
UFL_L3: J16.1, R36.1
UFL_L4: J19.1, R38.2
VDDA1: C13.2, C20.2, C21.2, D3.1, L1.4, U1.13
VDDA2: C46.2, C53.2, C54.2, D7.1, L8.4, U2.13
VDDB1: C16.2, C23.2, C25.2, D4.1, L2.4, U1.10
VDDB2: C49.2, C56.2, C58.2, D8.1, L9.4, U2.10
VDDI1: C19.2, R13.2, U1.7
VDDI2: C52.2, R32.2, U2.7
VEEA1: C14.2, C20.1, C22.1, L1.1, R14.1, U1.11
VEEA2: C47.2, C53.1, C55.1, L8.1, R33.1, U2.11
VEEB1: C15.2, C23.1, C24.1, L2.1, R15.1, U1.8
VEEB2: C48.2, C56.1, C57.1, L9.1, R34.1, U2.8
VINA_N1: J3.2, L1.2
VINA_N2: J12.2, L8.2
VINA_P1: J3.1, L1.3
VINA_P2: J12.1, L8.3
VINB_N1: J4.2, L2.2
VINB_N2: J13.2, L9.2
VINB_P1: J4.1, L2.3
VINB_P2: J13.1, L9.3

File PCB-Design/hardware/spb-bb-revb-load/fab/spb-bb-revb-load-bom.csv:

"# 4 layers, 1.6 mm FR4, 2 oz (70 um) on all layers, L1-L2 and L3-L4 prepreg 0.1 mm, ENIG; BLIND vias L1-L2 (0.25 mm drill) filled + capped in the LS source pads; load-test board; IPC class 2; solder mask over all copper and ALL vias tented (the 1200 V control/power barrier relies on it)"
Qty,References,Value,Footprint,Manufacturer part / note,Fit
2,J1 J2,DC+,Wuerth_REDCUBE-THR_WP-THRBU_74650174_THR,"Wuerth 74650174 (REDCUBE THR, M4)",fit
8,Q1 Q2 Q3 Q4 Q5 Q6 Q7 Q8,EPC2361,EPC2361,EPC2361,fit
40,C1 C10 C11 C12 C2 C26 C27 C28 C29 C3 C30 C31 C32 C33 C34 C35 C36 C37 C38 C39 C4 C40 C41 C42 C43 C44 C45 C5 C59 C6 C60 C61 C62 C63 C64 C65 C66 C7 C8 C9,1uF 100V X7S,C_0805_2012Metric_TightCrtYd,TDK C2012X7S2A105K125AB,fit
8,R1 R2 R20 R21 R22 R23 R3 R4,0R5 1% (R_G HL),R_0603_1608Metric,0.5R 0603 1% (Panasonic ERJ-3BQFR50V),fit
4,R24 R25 R5 R6,10k 1% (HS gate pull-down),R_0603_1608Metric,10k 0603 1%,fit
2,U1 U2,2EDF7275K,2EDF7275K_PG-TFLGA-13-4,Infineon 2EDF7275KXUMA1,fit
4,R26 R28 R7 R9,"0R75 1% (R_ON,A)",R_0603_1608Metric,0.75R 0603 1% (Panasonic ERJ-3RQFR75V),fit
4,R10 R27 R29 R8,"0R (R_OFF,A)",R_0603_1608Metric,0R 0603 jumper (set R_OFF here),fit
4,D1 D2 D5 D6,PMEG3020EJ,D_SOD-323F,"Nexperia PMEG3020EJ (30 V, 2 A, SOD323F)",fit
8,C13 C14 C15 C16 C46 C47 C48 C49,1uF 25V X7R 0603,C_0603_1608Metric,TDK C1608X7R1E105K080AB,fit
4,C17 C18 C50 C51,100pF C0G 0603,C_0603_1608Metric,Murata GRM1885C1H101JA01,fit
4,R11 R12 R30 R31,47R 1% (INA),R_0603_1608Metric,47R 0603 1%,fit
2,C19 C52,22nF 25V X7R 0603,C_0603_1608Metric,Murata GRM188R71E223KA01,fit
2,R13 R32,3k 1% (RVDDI),R_0603_1608Metric,3.0k 0603 1%,fit
4,J12 J13 J3 J4,"V_ISO,HS in: 1 +, 2 -",PinHeader_1x02_P2.54mm_Vertical,2.54 mm header 1x2,fit
13,L1 L10 L11 L12 L13 L2 L3 L4 L5 L6 L7 L8 L9,WE-CNSW 744232601,L_CommonMode_Wurth_WE-CNSW-1206,"Wurth 744232601 (600 Ohm @ 100 MHz, 260 mA)",fit
4,C20 C23 C53 C56,4.7uF 25V X7R 0805,C_0805_2012Metric,Murata GRM21BR71E475KA73,fit
4,D3 D4 D7 D8,BZX384-C5V1,D_SOD-323,"Nexperia BZX384-C5V1 (5.1 V, 300 mW)",fit
4,R14 R15 R33 R34,"150R 1% 0603 (bias, <= 82 mW)",R_0603_1608Metric,150R 0603 1% 0.1 W,fit
8,C21 C22 C24 C25 C54 C55 C57 C58,4.7uF 16V X5R 0603,C_0603_1608Metric,Murata GRM188R61C475KAAJ,fit
2,J14 J5,CTRL1: 1 RTN 2 PWMH 3 RTN 4 PWML 5 RTN 6 DIS 7 RTN 8 12V 9 RTN 10 NTC,PinHeader_2x05_P2.54mm_Vertical_SMD,"Samtec TSM-105-01-T-DV (2 x 5, 2.54 mm, SMT)",fit
2,FB1 FB2,BLM18PG221SN1 (220 R @ 100 MHz),L_0603_1608Metric,"Murata BLM18PG221SN1D (ferrite bead, 1.4 A)",fit
1,RT1,NTC 10k B3380 0603,R_0603_1608Metric,Murata NCP18XH103F03RB,fit
8,J10 J15 J16 J18 J19 J6 J7 J9,U.FL H1,U.FL_Hirose_U.FL-R-SMT-1_Vertical,Hirose U.FL-R-SMT-1(10),fit
8,R16 R17 R18 R19 R35 R36 R37 R38,0R (V_GS HS),R_0603_1608Metric,0R 0603,fit
4,J11 J17 J20 J8,U.FL D1,U.FL_Hirose_U.FL-R-SMT-1_Vertical,"Hirose U.FL-R-SMT-1(01) - 100 V listed, confirm",fit
20,C67 C68 C69 C70 C71 C72 C73 C74 C75 C76 C77 C78 C79 C80 C81 C82 C83 C84 C85 C86,22uF 100V X7S 2220,C_2220_5750Metric_TightCrtYd,TDK C5750X7S2A226M280KB,fit
2,R39 R40,68k 1206 (HV LED),R_1206_3216Metric,68k 1206 1% 200 V,fit
1,D9,red 0603 (DC link present),LED_0603_1608Metric,Wurth 150060RS75000,fit
1,R41,100k 1206 (bleeder),R_1206_3216Metric,100k 1206 1% 200 V,fit

Mechanical (not placed by the assembler)
1,HS1,"Fan heatsink 40 x 40 x 50 mm, 12 V fan",-,"Fischer Elektronik LAM 4 K 50 12 (0.65 K/W), Farnell 4708974"
1,HS1,Fan supply: 12 V from the bench supply (no fan header on the board: 1200 V barrier),-,-
2,"J5, J14",Control cable: 2 x 5 IDC socket + ribbon (each signal next to its own return),-,"2.54 mm IDC, e.g. Wurth 61201021621"
1,HS1,"Heat spreader Al 6061, 89.5 x 12.8 x 3 mm, 4 pedestals 5.6 x 7.7 x 0.6 mm over the cells, 3 x M2.5 (H5-H7)",-,machined
4,HS1,"Insulating gap pad over each cell, 5.6 x 7.7 mm, 0.5 mm, >= 5 W/mK",-,"Bergquist TGP 5000 0.020 in, cut to size, or equivalent"
3,H5-H7,M2.5 x 10 screw + insulating shoulder washer (spreader),-,nylon or steel + washer
4,H1-H4,M2.5 standoff + screw (H3/H4: nylon M2.5 x 6.5 mm onto the busbar),-,nylon
2,J1-J2,M4 x 8 screw + washer from below through the busbar into the REDCUBE,-,"steel, A2"
1,J22,"M6 x 16 bolt + nut + 2 washers, AC bolt pad",-,"steel, A2"
1,J22,AC bar 12 x 5 mm Cu through a LEM HO 250-S,-,Cu-ETP + LEM HO 250-S
